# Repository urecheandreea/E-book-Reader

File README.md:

# E-book-Reader
## Hardware 
**OpenBook** is an open-source, portable e-reader powered by the **ESP32-C6-WROOM-1-N8** microcontroller.
### Microcontroller - **ESP32-C6-WROOM-1-N8**
  - 32-bit RISC-V @ 160 MHz
  - 8MB internal flash
  - Supports **Wi-Fi 6 (802.11ax)** and **Bluetooth 5.0 LE**
  - Interfaces used:
    - **SPI** (for E-Ink display, Flash, SD card)
    - **I2C** (for sensors and RTC)
    - **UART**, **GPIO**, **PWM**
### E-Ink Display
- **E-Ink screen** connected via SPI:
  - MOSI: GPIO18  
  - MISO: GPIO19  
  - CLK: GPIO20  
  - CS: GPIO21  
- Power is controlled via MOSFET (Q3 - S1B126DT1-GE3) to save energy.
- Display type selection is done via jumper (S11, P2).
##  Storage
- **MicroSD Card**
  - Connected via SPI (CS: GPIO9)
  - Used for storing files and data logging
- **NOR Flash – W25Q512JVEIQ**
  - 64MB external flash via SPI
##  Sensors
- **BME688** – Measures temperature, pressure, humidity, and air quality  
- **DS3231SN** – High-precision Real-Time Clock (RTC)  
- **MAX17048G+T10** – Battery fuel gauge (State of Charge)
- All sensors are connected via the **I2C** bus:
  - SDA: GPIO6  
  - SCL: GPIO7  
##  Power Management
- **USB-C connector**
  - Used for charging and possible data transfer
  - Includes CC identification and ESD protection
- **MCP73831** – LiPo battery charging IC
- **XC6220A331MR-G** – Low dropout regulators for 3.3V power
- EPD and I2C power rails are individually controlled via MOSFETs
- ESD protection on USB and SPI lines (USBLC6-2SC6Y, SD05B05V2L)
## Interfaces & Expandability
- **QWIIC / Stemma QT connector**
  - Easy expansion via plug-and-play I2C modules
- **Test Pads**
  - Breakout access to GPIO, UART, I2C for debugging
- **Control buttons**
  - RESET and BOOT
- **Status LEDs** for user feedback

## Power Consumption Summary
| Component              | Active (mA) | Sleep (mA) | Notes                             |
|-----------------------|-------------|------------|-----------------------------------|
| **ESP32-C6**          | ~80–100     | ~0.02      | Depends on Wi-Fi & sleep mode     |
| **E-Paper Display**   | ~26         | ~0.01      | Only during refresh               |
| **BME688 Sensor**     | ~2.1        | ~0.15      | Sleep mode available              |
| **RTC DS3231**        | ~0.2        | ~0.2       | Constant low power                |
| **MicroSD Card**      | ~30–100     | ~0.2       | Depends on access frequency       |
| **W25Q512JVEIQ Flash**| ~10–20      | ~0.01      | During SPI read/write             |
## ESP32-C6 Pin Usage
| Component              | ESP32-C6 Pin(s)                          | Interface | Purpose                                                             |
|------------------------|------------------------------------------|-----------|---------------------------------------------------------------------|
| E-Paper Display        | GPIO7 (MOSI), GPIO6 (SCK), GPIO10 (CS), GPIO5 (DC), GPIO23 (RST), GPIO3 (BUSY) | SPI | Transfers image data to the display and controls its state         |
| MicroSD Card           | GPIO7 (MOSI), GPIO6 (SCK), GPIO4 (CS_SD), GPIO2 (MISO)                        | SPI | Allows storage and retrieval of e-book files                        |
| BME688 Sensor          | GPIO21 (SDA), GPIO22 (SCL)                                                   | I2C | Reads temperature, humidity, pressure, and air quality             |
| RTC Module (DS3231)    | GPIO21 (SDA), GPIO22 (SCL), GPIO18 (RST), GPIO1 (32KHz, optional), GPIO0 (INT_RTC, optional) | I2C | Keeps track of time even when the ESP32 is off                     |
| NOR Flash (W25Q512J)   | GPIO11 (CS_FLASH), GPIO6 (SCK), GPIO2 (MISO), GPIO7 (MOSI)                   | SPI | Additional non-volatile storage                                     |
| Battery Fuel Gauge     | GPIO21 (SDA), GPIO22 (SCL)                                                   | I2C | Monitors battery level and charge status                            |
| USB-C Connector        | Via LDO regulator to 3.3V power rail                                          | USB | Supplies power and programming interface for the ESP32-C6          |
| Control Buttons        | GPIO9 (BOOT), GPIO15 (CHANGE), EN (RESET)                                    | GPIO | User input for device interaction and hardware reset                |

## Block Diagram

## Bill Of Materials
| Component                            | Link                                                                                             | Datasheet                                                                 |
|-------------------------------------|--------------------------------------------------------------------------------------------------|---------------------------------------------------------------------------|
| ESP32-C6-WROOM-1-N8                 | [SnapEDA](https://www.snapeda.com/parts/ESP32-C6-WROOM-1-N8/Espressif+Systems/view-part/?ref=eda) | [Datasheet](https://www.snapeda.com/parts/ESP32-C6-WROOM-1-N8/Espressif%20Systems/datasheet/) |
| MCP73831T-2ACI/OT – PMIC            | [SnapEDA](https://www.snapeda.com/parts/MCP73831T-2ACI/OT/Microchip/datasheet/)                  | [Datasheet](https://www.snapeda.com/parts/MCP73831T-2ACI/OT/Microchip/datasheet/)             |
| MAX17048G+T10 – Fuel Gauge          | [SnapEDA](https://www.snapeda.com/parts/MAX17048G+T10/Analog+Devices/view-part/?ref=eda)         | [Datasheet](https://www.snapeda.com/parts/MAX17048G+T10/Analog%20Devices/datasheet/)          |
| BME680 – Environmental Sensor       | [SnapEDA](https://www.snapeda.com/parts/BME680/Bosch/view-part/?welcome=home)                    | [Datasheet](https://www.bosch-sensortec.com/media/boschsensortec/downloads/datasheets/bst-bme680-ds001.pdf) |
| DS3231SN – RTC                      | [SnapEDA](https://www.snapeda.com/parts/DS3231SN%23/Analog+Devices/view-part/?ref=eda)           | [Datasheet](https://www.snapeda.com/parts/DS3231SN%23/Analog%20Devices/datasheet/)            |
| W25Q512JVEIQ – SPI Flash            | [SnapEDA](https://www.snapeda.com/parts/W25Q512JVEIQ/Winbond+Electronics/view-part/?ref=eda)    | [Datasheet](https://www.winbond.com/resource-files/W25Q512JV%20SPI%20RevB%2006252019%20KMS.pdf) |
| QWIIC Connector                     | [SnapEDA](https://www.snapeda.com/parts/PRT-14417/SparkFun/view-part/)                          | [Datasheet](https://www.snapeda.com/parts/PRT-14417/SparkFun%20Electronics/datasheet/)        |
| USB4110-GF-A – USB-C Connector      | [ComponentSearchEngine](https://componentsearchengine.com/part-view/USB4110-GF-A/GCT%20(GLOBAL%20CONNECTOR%20TECHNOLOGY)) | [Datasheet](https://gct.co/files/drawings/usb4110.pdf) |
| FH34SRJ-24S-0.5SH – FFC Connector   | [Mouser](https://ro.mouser.com/ProductDetail/Hirose-Connector/FH34SRJ-24S-0.5SH99?qs=vcbW%252B4%252BSTIpKBl5ap9J8Fw%3D%3D) | [Datasheet](https://www.snapeda.com/parts/FH34SRJ-24S-0.5SH(99)/Hirose%20Connector/datasheet/) |
| KP-1608SURCK – LED 0603             | [SnapEDA](https://www.snapeda.com/parts/KP-1608SURCK/Kingbright/view-part/?ref=search&t=LED%200603) | [Datasheet](https://www.snapeda.com/parts/KP-1608SURCK/Kingbright/datasheet/)                |
| EVQPUJ02K – Custom Button           | [Panasonic](https://industry.panasonic.com/global/en/products/control/switch/light-touch/number/evqpuj02k) | [Datasheet](https://industry.panasonic.com/global/en/downloads?tab=catalog&small_g_cd=203&part_no=EVQPUJ02K) |
| CPH3225A – RTC Crystal              | [SnapEDA](https://www.snapeda.com/parts/CPH3225A/Seiko+Instruments/view-part/?ref=snap)          | [Datasheet](https://www.snapeda.com/parts/CPH3225A/Seiko%20Instruments/datasheet/)            |
| BD5229G-TR – Reset IC               | [ComponentSearchEngine](https://componentsearchengine.com/part-view/BD5229G-TR/ROHM%20Semiconductor) | [Datasheet](https://fscdn.rohm.com/en/products/databook/datasheet/ic/power/voltage_detector/bd52xxg-e.pdf) |
| XC6220A331MR-G – LDO Regulator      | [ComponentSearchEngine](https://componentsearchengine.com/part-view/XC6220A331MR-G/Torex)         | [Datasheet](https://product.torexsemi.com/system/files/series/xc6220.pdf)                     |
| 744043680 – Inductor                | [Mouser](https://ro.mouser.com/ProductDetail/Wurth-Elektronik/744043680?qs=PGXP4M47uW6VkZq%252BkzjrHA%3D%3D) | [Datasheet](https://www.we-online.com/components/products/datasheet/744043680.pdf)            |
| SI1308EDL – MOSFET                  | [SnapEDA](https://www.snapeda.com/parts/SI1308EDL-T1-GE3/Vishay+Siliconix/view-part/?welcome=home&ref=eda) | [Datasheet](https://www.snapeda.com/parts/SI1308EDL-T1-GE3/Vishay%20Siliconix/datasheet/)     |
| MBR0530 – Schottky Diode           | [SnapEDA](https://www.snapeda.com/parts/MBR0530/Onsemi/view-part/?ref=snap)                      | [Datasheet](https://www.snapeda.com/parts/MBR0530/ON%20Semiconductor/datasheet/)              |
| USBLC6-2SC6Y – ESD Protection       | [SnapEDA](https://www.snapeda.com/parts/USBLC6-2SC6Y/STMicroelectronics/view-part/?welcome=home&ref=eda) | [Datasheet](https://www.snapeda.com/parts/USBLC6-2SC6Y/STMicroelectronics/datasheet/)         |
| PGB1010603MR – TVS Protection       | [SnapEDA](https://www.snapeda.com/parts/PGB1010603MR/Littelfuse/view-part/?ref=eda)              | [Datasheet](https://www.snapeda.com/parts/PGB1010603MR/Littelfuse%20Inc./datasheet/)          |
| 112A-TAAR-R03 – Pin Header          | [Comet](https://store.comet.srl.ro/Catalogue/Product/43497/)                                     | [Datasheet](https://www.snapeda.com/parts/112A-TAAR-R03/Attend/datasheet/)                    |
| 0402 Ceramic Capacitor             | [Mouser](https://ro.mouser.com/c/passive-components/capacitors/ceramic-capacitors/?q=CC0402)     | [Datasheet](https://componentsearchengine.com/Datasheets/2/CC0402MRX5R5BB106.pdf)             |
| 0402 Resistor                      | [GrabCAD](https://grabcad.com/library/resistor-0402-1)                                            | [Datasheet](https://www.yageo.com/upload/media/product/products/datasheet/rchip/PYu-RC_Group_51_RoHS_L_12.pdf) |
| TAJB475K025RNJ – 3528 Tantalum Cap | [SnapEDA](https://www.snapeda.com/parts/TAJB475K025RNJ/AVX%20Corporation/view-part/?ref=eda)     | [Datasheet](https://s3.amazonaws.com/snapeda/datasheet/TAJB475K025RNJ_AVX.pdf)               |
| SJ -SMD solder JUMPER              | [GrabCAD](https://grabcad.com/library/solder-jumpers-1)                                          | [DataSheet](https://www.farnell.com/datasheets/2813407.pdf)                                  |
| PFMF.050.1-ESP32C6_VARISTORCN1812  | [Mouser](https://www.mouser.co.uk/ProductDetail/EPCOS-TDK/B72520T0350K062?qs=dEfas%2FXlABIszF52uu7vrg%3D%3D)| [DataSheet](https://www.tdk-electronics.tdk.com/inf/75/db/CTVS_14/Surge_protection_series.pdf)  | 

## Implementation Steps
Creating the schematic according to the diagram,Finding and loading 3D models for each component,Designing the PCB,Placing the components on the PCB,Routing,Creating ground planes, via-stitching,Meeting requirements (component names on top silkscreen, DRC clean, etc.),Creating the battery and display,Assembling everything into the enclosure.

I only approved the "SMD-Hole, Board Outline Clearance" errors, as this was previously accepted and specified.

## Issues encountered:
I had to manually add the 3D model for EACH component because I had problems and errors when trying to update the library (adding to the library wasn't working), which was extremely time-consuming.

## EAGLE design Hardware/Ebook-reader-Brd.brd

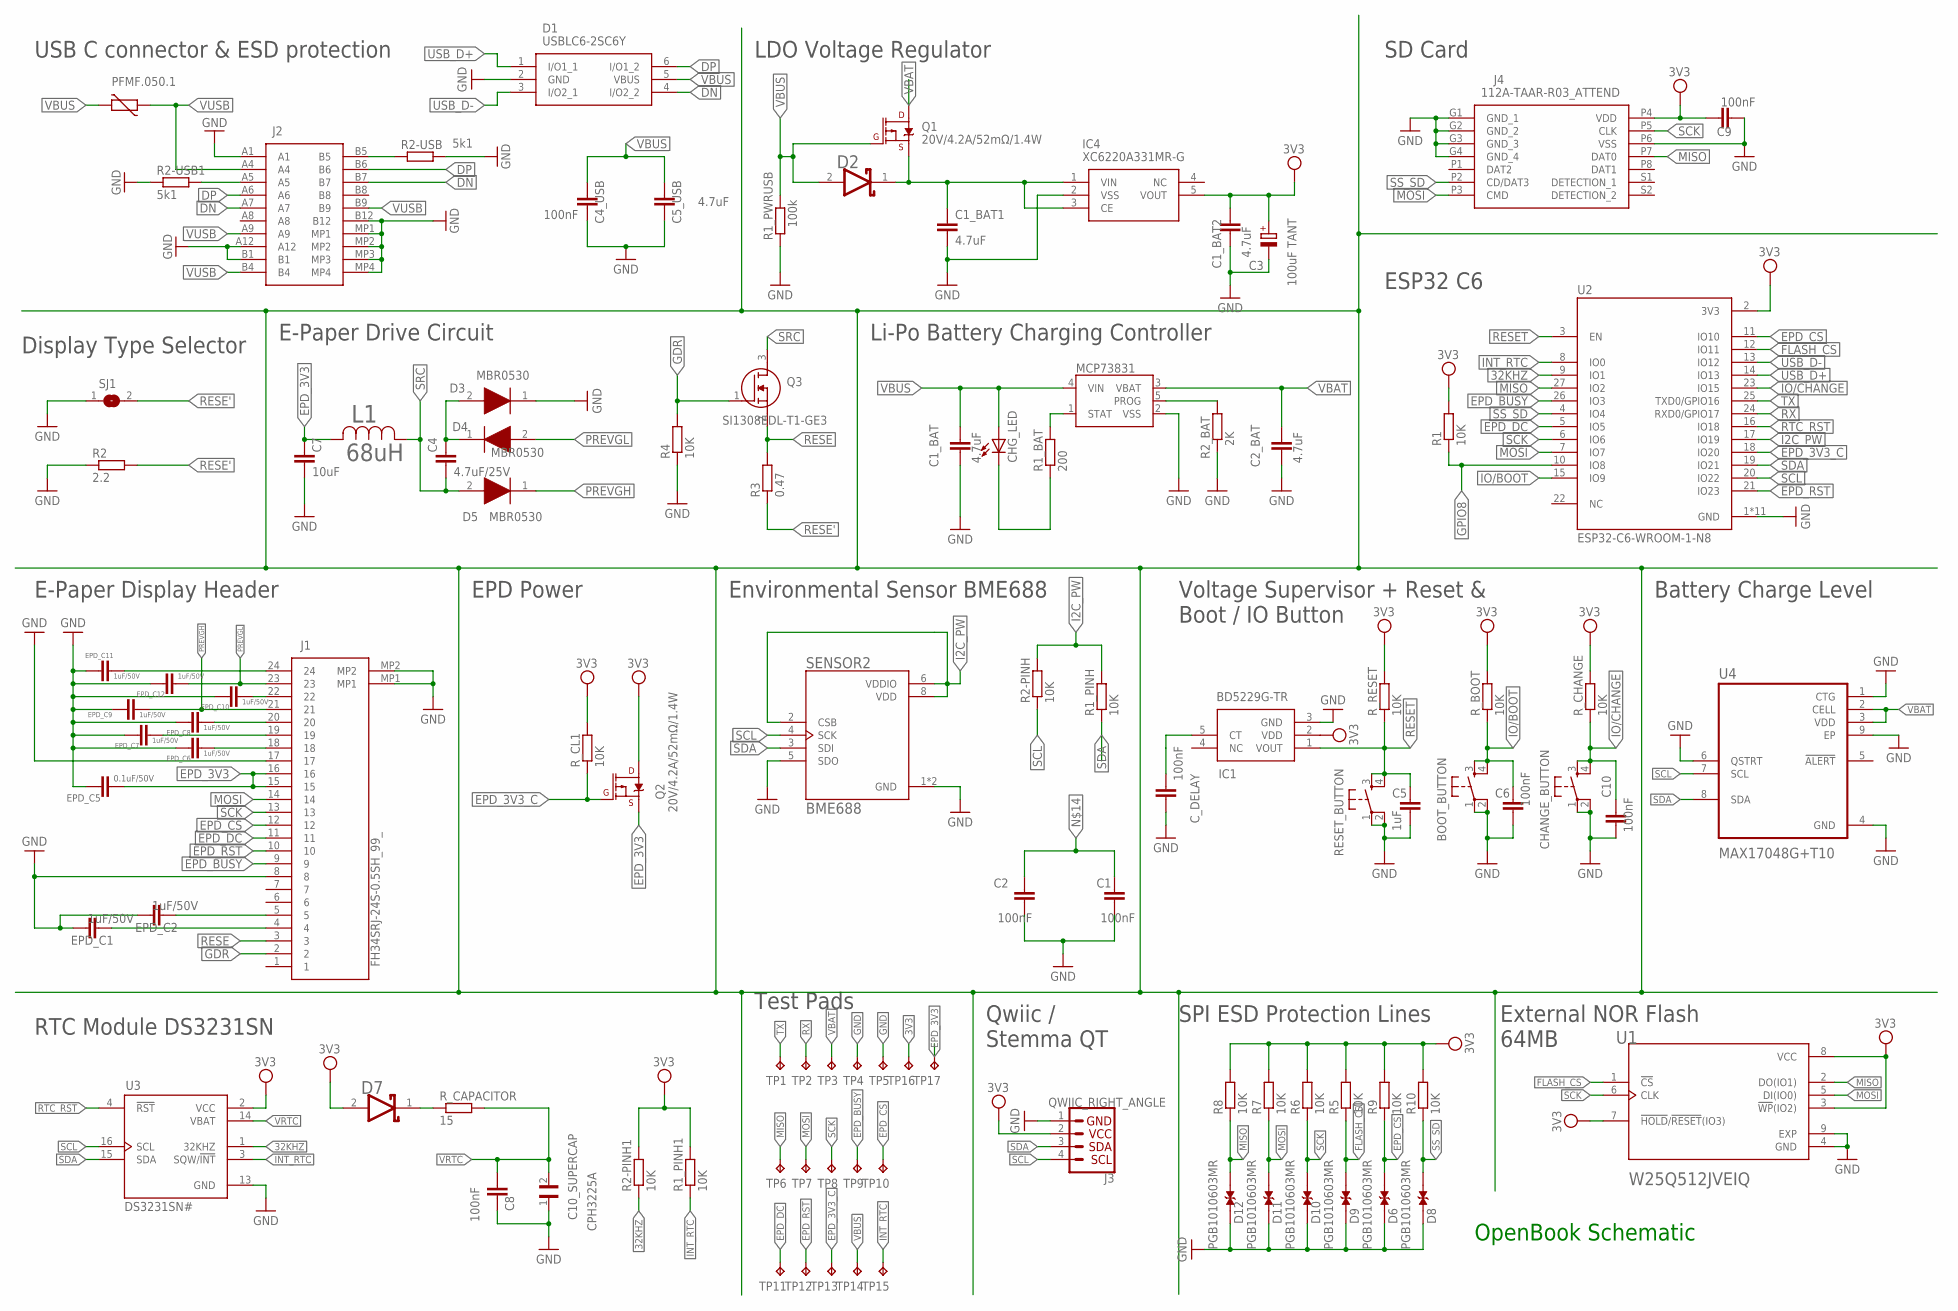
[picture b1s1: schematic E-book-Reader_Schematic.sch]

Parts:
BOOT_BUTTON: BOOT_BUTTON; MYBUTTON
C1, C2, C6, C9, C10: 100nF; EAGLE-LTSPICE_C0402
C1_BAT, C1_BAT1, C1_BAT2, C2_BAT, C5_USB: 4.7uF; EAGLE-LTSPICE_C0402
C3: 100uF TANT; RCL_CT3528
C4: 4.7uF/25V; ESP32_WROVER_EAGLE-LTSPICE_C0402
C4_USB, C8: 100nF; ESP32_WROVER_EAGLE-LTSPICE_C0402
C5: 1uF; EAGLE-LTSPICE_C0402
C7: 10uF; ESP32_WROVER_EAGLE-LTSPICE_C0402
C10_SUPERCAP: CPH3225A; CAPCP3225X100N
CHANGE_BUTTON: CHANGE_BUTTON; MYBUTTON
CHG_LED: ADAFRUIT_LEDCHIP-LED0603; ADAFRUIT_CHIP-LED0603
C_DELAY: 100nF; EAGLE-LTSPICE_C0402
D1: USBLC6-2SC6Y; SOT95P280X145-6N
D2: ESP32_WROVER_AVX---SD0805S020S1R0_AVX_SD0805S020S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; ESP32_WROVER_AVX---SD0805S020S1R0_AVX_SD0805S020S1R0_0
D3, D4, D5: MBR0530; SOD3716X135N
D6, D8, D9, D10, D11, D12: PGB1010603MR; DIOC1608X36N
D7: SD0805S020S1R0; ESP32_WROVER_AVX---SD0805S020S1R0_AVX_SD0805S020S1R0_0
EPD_C1, EPD_C2, EPD_C6, EPD_C7, EPD_C8, EPD_C9, EPD_C10, EPD_C11, EPD_C12: 1uF/50V; ESP32_WROVER_EAGLE-LTSPICE_C0402
EPD_C5: 0.1uF/50V; ESP32_WROVER_EAGLE-LTSPICE_C0402
IC1: BD5229G-TR; SOT95P280X125-5N
IC4: XC6220A331MR-G; SOT95P280X120-5N
J1: FH34SRJ-24S-0.5SH_99_; FH34SRJ24S05SH99
J2: SAMACSYS_PARTS_USB4110-GF-A; SAMACSYS_PARTS_USB4110GFA
J3: QWIIC_RIGHT_ANGLE; JST04_1MM_RA
J4: 112A-TAAR-R03_ATTEND; 112ATAARR03ATTEND
L1: 68uH; IND_4828-WE-TPC_WRE
MCP73831: ESP32_WROVER_SPARKFUN-IC-POWER_MCP73831; ESP32_WROVER_SPARKFUN-IC-POWER_SOT23-5
PFMF.050.1: ESP32C6_VARISTORCN1812; ESP32C6_VARISTOR_CT/CN1812
Q1, Q2: 20V/4.2A/52mΩ/1.4W; ESP32_WROVER_SPARKFUN-DISCRETESEMI_SOT23-3
Q3: SI1308EDL-T1-GE3; SOT65P210X110-3N
R1, R1_PINH, R1_PINH1, R2-PINH, R2-PINH1, R4, R5, R6, R7, R8, R9, R10: 10K; ESP32_WROVER_EAGLE-LTSPICE_R0402
R1_BAT: 200; ESP32_WROVER_EAGLE-LTSPICE_R0402
R1_PWRUSB: 100k; ESP32_WROVER_EAGLE-LTSPICE_R0402
R2: 2.2; ESP32_WROVER_EAGLE-LTSPICE_R0402
R2-USB, R2-USB1: 5k1; ESP32_WROVER_EAGLE-LTSPICE_R0402
R2_BAT: 2K; ESP32_WROVER_EAGLE-LTSPICE_R0402
R3: 0.47; ESP32_WROVER_EAGLE-LTSPICE_R0402
RESET_BUTTON: RESET_BUTTON; MYBUTTON
R_BOOT: 10K; ESP32_WROVER_EAGLE-LTSPICE_R0402
R_CAPACITOR: 15; ESP32_WROVER_EAGLE-LTSPICE_R0402
R_CHANGE: 10K; ESP32_WROVER_EAGLE-LTSPICE_R0402
R_CL1: 10K; ESP32_WROVER_EAGLE-LTSPICE_R0402
R_RESET: 10K; ESP32_WROVER_EAGLE-LTSPICE_R0402
SENSOR2: BME688; ESP32_WROVER_BME680_PSON80P300X300X100-8N
SJ1: SJ
TP1, TP2, TP3, TP4, TP5, TP6, TP7, TP8, TP9, TP10, TP11, TP12, TP13, TP14, TP15, TP16, TP17: TPTP20R; TP20R
U1: W25Q512JVEIQ; SON127P600X800X80-9N
U2: ESP32-C6-WROOM-1-N8; XCVR_ESP32-C6-WROOM-1-N8
U3: DS3231SN#; SOIC127P1032X265-16N
U4: MAX17048G+T10; SON50P200X200X80-9N

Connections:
3V3: C1_BAT2.1, C3.+, C9.1, D7.2 (ANODE), IC1.2 (VDD), IC4.5 (VOUT), J3.2, J4.P4 (VDD), Q2.3 (D), R1.2, R1_PINH1.2, R2-PINH1.2, R5.2, R6.2, R7.2, R8.2, R9.2, R10.2, R_BOOT.2, R_CHANGE.2, R_CL1.2, R_RESET.2, TP16.TP, U1.3 (!WP!(IO2)), U1.7 (!HOLD!/!RESET!(IO3)), U1.8 (VCC), U2.2 (3V3), U3.2 (VCC)
32KHZ: R2-PINH1.1, U2.9 (IO1), U3.1 (32KHZ)
DN: D1.4 (I/O2_2), J2.A7, J2.B7
DP: D1.6 (I/O1_2), J2.A6, J2.B6
EPD_3V3: C7.1, EPD_C5.1, J1.15, J1.16, L1.2, Q2.2 (S), TP17.TP
EPD_3V3_C: Q2.1 (G), R_CL1.1, TP13.TP, U2.18 (IO20)
EPD_BUSY: J1.9, TP9.TP, U2.26 (IO3)
EPD_CS: D6.2, J1.12, R9.1, TP10.TP, U2.11 (IO10)
EPD_DC: J1.11, TP11.TP, U2.5 (IO5)
EPD_RST: J1.10, TP12.TP, U2.21 (IO23)
FLASH_CS: D9.2, R5.1, U1.1 (!CS), U2.12 (IO11)
GDR: J1.2, Q3.1 (G), R4.2
GND: BOOT_BUTTON.1, BOOT_BUTTON.2, C1.2, C1_BAT.2, C1_BAT1.2, C1_BAT2.2, C2.2, C2_BAT.2, C3.-, C4_USB.2, C5.2, C5_USB.2, C6.2, C7.2, C8.2, C9.2, C10.2, C10_SUPERCAP.1, CHANGE_BUTTON.1, CHANGE_BUTTON.2, C_DELAY.2, D1.2 (GND), D3.1 (K), D6.1, D8.1, D9.1, D10.1, D11.1, D12.1, EPD_C1.2, EPD_C2.2, EPD_C5.2, EPD_C6.2, EPD_C7.2, EPD_C8.2, EPD_C9.2, EPD_C10.2, EPD_C11.2, EPD_C12.2, IC1.3 (GND), IC4.2 (VSS), J1.8, J1.17, J1.MP1, J1.MP2, J2.A1, J2.A12, J2.B1, J2.B12, J2.MP1, J2.MP2, J2.MP3, J2.MP4, J3.1, J4.G1 (GND_1), J4.G2 (GND_2), J4.G3 (GND_3), J4.G4 (GND_4), J4.P6 (VSS), MCP73831.2 (VSS), R1_PWRUSB.1, R2.1, R2-USB.2, R2-USB1.1, R2_BAT.1, R4.1, RESET_BUTTON.1, RESET_BUTTON.2, SENSOR2.1 (GND), SENSOR2.5 (SDO), SENSOR2.7 (GND), SJ1.1, TP4.TP, TP5.TP, U1.4 (GND), U1.9 (EXP), U2.1 (GND), U2.28 (GND), U2.29_1 (GND), U2.29_2 (GND), U2.29_3 (GND), U2.29_4 (GND), U2.29_5 (GND), U2.29_6 (GND), U2.29_7 (GND), U2.29_8 (GND), U2.29_9 (GND), U3.13 (GND), U4.1 (CTG), U4.4 (GND), U4.6 (QSTRT), U4.9 (EP)
GPIO8: R1.1, U2.10 (IO8)
I2C_PW: R1_PINH.2, R2-PINH.2, SENSOR2.2 (CSB), SENSOR2.6 (VDDIO), SENSOR2.8 (VDD), U2.17 (IO19)
INT_RTC: R1_PINH1.1, TP15.TP, U2.8 (IO0), U3.3 (SQW/!INT)
IO/BOOT: BOOT_BUTTON.3, BOOT_BUTTON.4, C6.1, R_BOOT.1, U2.15 (IO9)
IO/CHANGE: C10.1, CHANGE_BUTTON.3, CHANGE_BUTTON.4, R_CHANGE.1, U2.23 (IO15)
MISO: D12.2, J4.P7 (DAT0), R8.1, TP6.TP, U1.2 (DO(IO1)), U2.27 (IO2)
MOSI: D11.2, J1.14, J4.P3 (CMD), R7.1, TP7.TP, U1.5 (DI(IO0)), U2.7 (IO7)
unnamed: MCP73831.5 (PROG), R2_BAT.2
unnamed: C4.1, D3.2 (A), D4.1 (K)
unnamed: J2.A5, R2-USB1.2
unnamed: C1_BAT1.1, D2.1 (CATHODE), IC4.1 (VIN), IC4.3 (CE), Q1.2 (S)
unnamed: MCP73831.1 (STAT), R1_BAT.2
unnamed: CHG_LED.C, R1_BAT.1
unnamed: EPD_C1.1, J1.4
unnamed: EPD_C2.1, J1.5
unnamed: J2.B5, R2-USB.1
unnamed: EPD_C10.1, J1.22
unnamed: C_DELAY.1, IC1.5 (CT)
unnamed: C1.1, C2.1
unnamed: D7.1 (CATHODE), R_CAPACITOR.1
unnamed: EPD_C8.1, J1.20
unnamed: EPD_C11.1, J1.24
unnamed: EPD_C7.1, J1.19
unnamed: EPD_C6.1, J1.18
PREVGH: D5.1 (K), EPD_C9.1, J1.21
PREVGL: D4.2 (A), EPD_C12.1, J1.23
RESE: J1.3, Q3.2 (S), R3.2
RESE': R2.2, R3.1, SJ1.2
RESET: C5.1, IC1.1 (VOUT), RESET_BUTTON.3, RESET_BUTTON.4, R_RESET.1, U2.3 (EN)
RTC_RST: U2.16 (IO18), U3.4 (!RST)
RX: TP2.TP, U2.24 (RXD0/GPIO17)
SCK: D10.2, J1.13, J4.P5 (CLK), R6.1, TP8.TP, U1.6 (CLK), U2.6 (IO6)
SCL: J3.4, R2-PINH.1, SENSOR2.4 (SCK), U2.20 (IO22), U3.16 (SCL), U4.7 (SCL)
SDA: J3.3, R1_PINH.1, SENSOR2.3 (SDI), U2.19 (IO21), U3.15 (SDA), U4.8 (SDA)
SRC: C4.2, D5.2 (A), L1.1, Q3.3 (D)
SS_SD: D8.2, J4.P2 (CD/DAT3), R10.1, U2.4 (IO4)
TX: TP1.TP, U2.25 (TXD0/GPIO16)
USB_D+: D1.1 (I/O1_1), U2.14 (IO13)
USB_D-: D1.3 (I/O2_1), U2.13 (IO12)
VBAT: C2_BAT.1, MCP73831.3 (VBAT), Q1.3 (D), TP3.TP, U4.2 (CELL), U4.3 (VDD)
VBUS: C1_BAT.1, C4_USB.1, C5_USB.1, CHG_LED.A, D1.5 (VBUS), D2.2 (ANODE), MCP73831.4 (VIN), PFMF.050.1.2, Q1.1 (G), R1_PWRUSB.2, TP14.TP
VRTC: C8.1, C10_SUPERCAP.2, R_CAPACITOR.2, U3.14 (VBAT)
VUSB: J2.A4, J2.A9, J2.B4, J2.B9, PFMF.050.1.1

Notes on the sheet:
USB C connector & ESD protection
LDO Voltage Regulator
SD Card
Display Type Selector
E-Paper Drive Circuit
Li-Po Battery Charging Controller
ESP32 C6
E-Paper Display Header
EPD Power
Environmental Sensor BME688
Voltage Supervisor + Reset & Boot / IO Button
Battery Charge Level
RTC Module DS3231SN
Test Pads
Qwiic / Stemma QT
SPI ESD Protection Lines
External NOR Flash 64MB
OpenBook Schematic

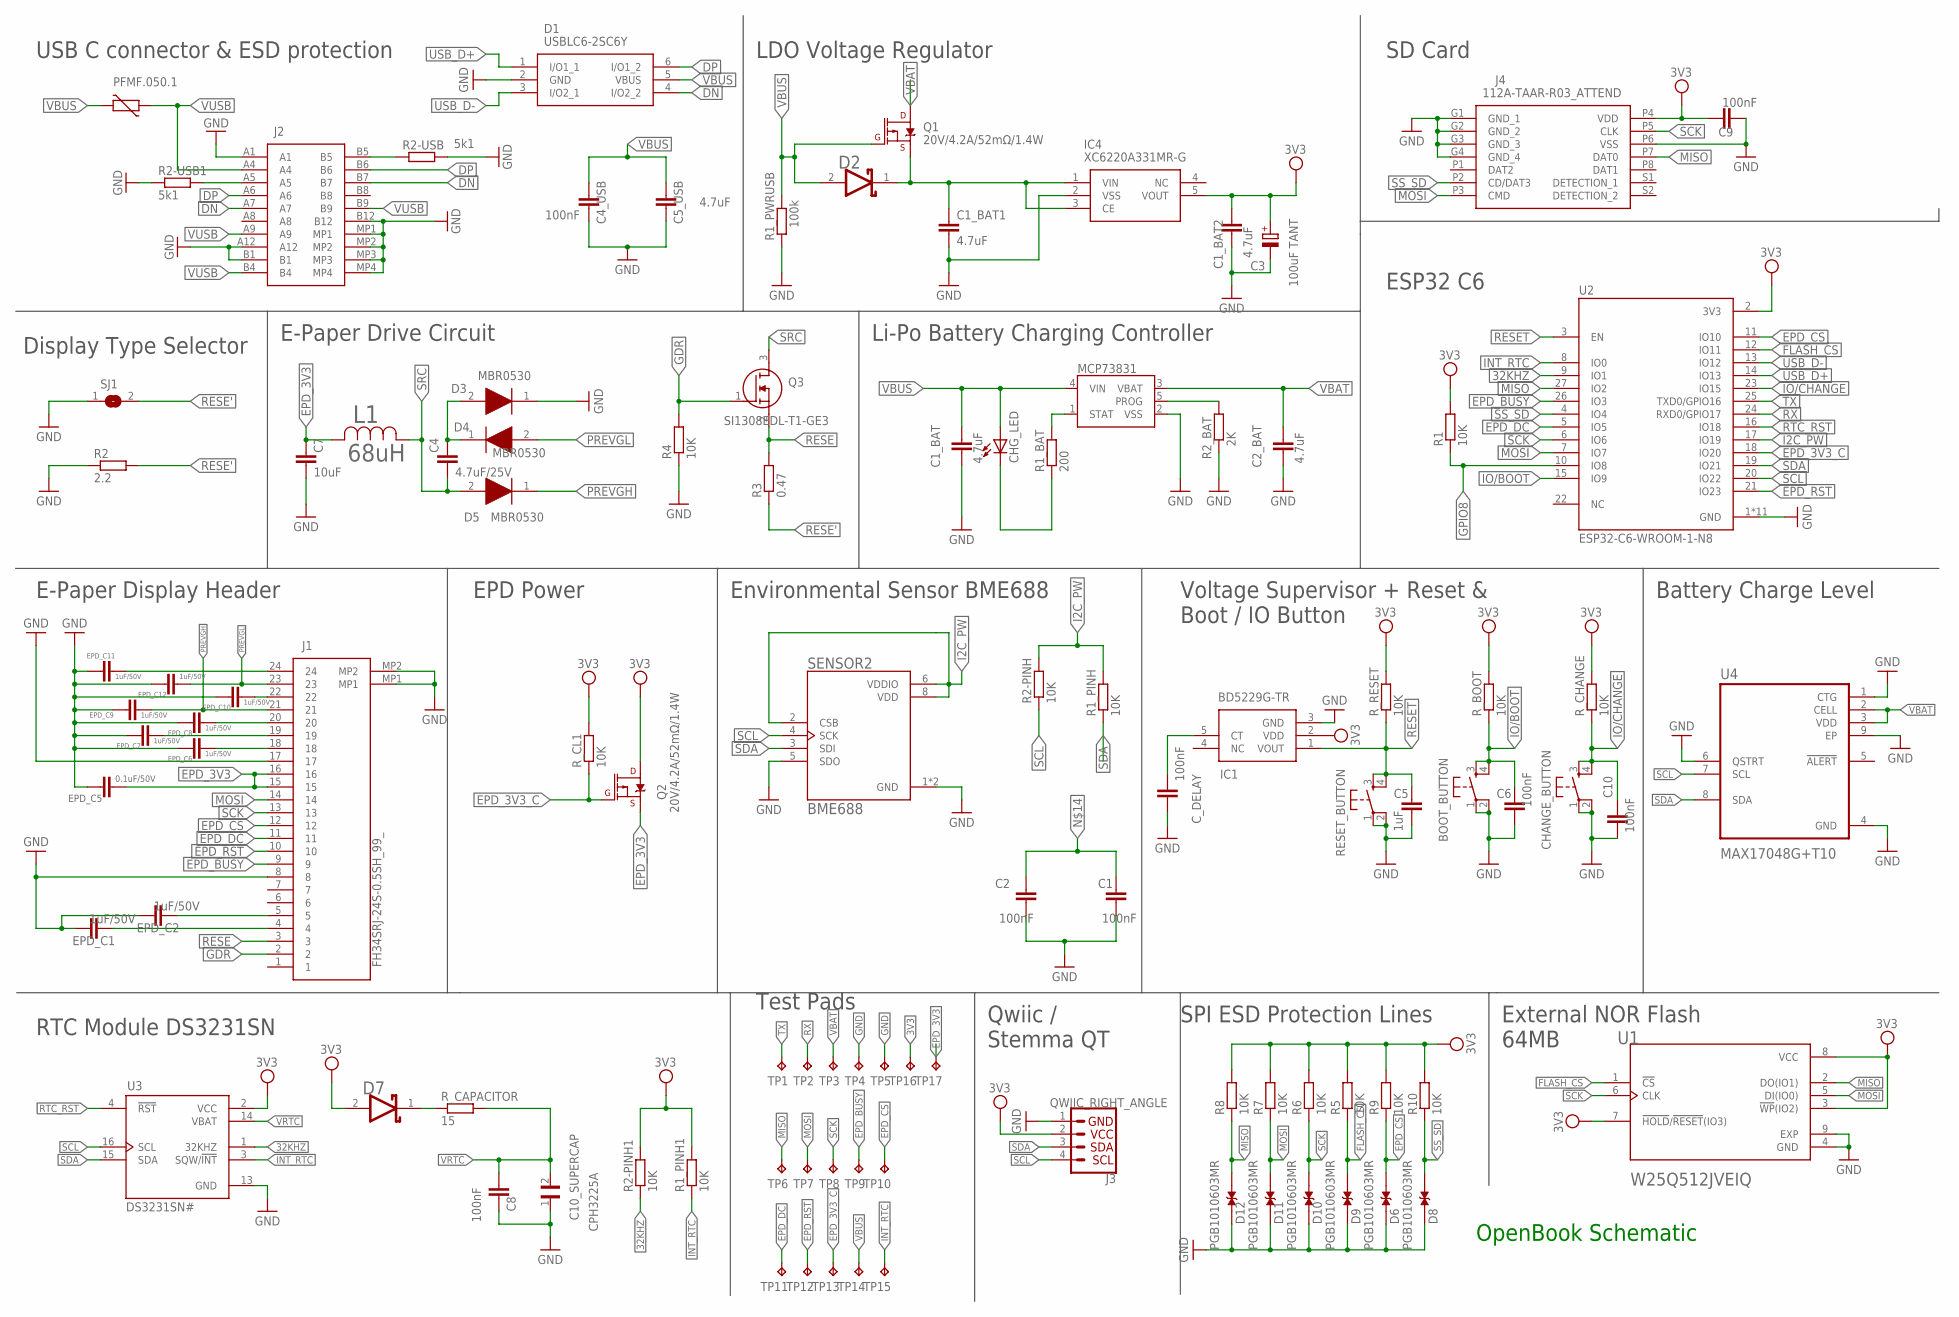
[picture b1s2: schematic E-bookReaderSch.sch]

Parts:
BOOT_BUTTON: BOOT_BUTTON; MYBUTTON
C1, C2, C6, C9, C10: 100nF; EAGLE-LTSPICE_C0402
C1_BAT, C1_BAT1, C1_BAT2, C2_BAT, C5_USB: 4.7uF; EAGLE-LTSPICE_C0402
C3: 100uF TANT; RCL_CT3528
C4: 4.7uF/25V; ESP32_WROVER_EAGLE-LTSPICE_C0402
C4_USB, C8: 100nF; ESP32_WROVER_EAGLE-LTSPICE_C0402
C5: 1uF; EAGLE-LTSPICE_C0402
C7: 10uF; ESP32_WROVER_EAGLE-LTSPICE_C0402
C10_SUPERCAP: CPH3225A; CAPCP3225X100N
CHANGE_BUTTON: CHANGE_BUTTON; MYBUTTON
CHG_LED: ADAFRUIT_LEDCHIP-LED0603; ADAFRUIT_CHIP-LED0603
C_DELAY: 100nF; EAGLE-LTSPICE_C0402
D1: USBLC6-2SC6Y; SOT95P280X145-6N
D2: ESP32_WROVER_AVX---SD0805S020S1R0_AVX_SD0805S020S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; ESP32_WROVER_AVX---SD0805S020S1R0_AVX_SD0805S020S1R0_0
D3, D4, D5: MBR0530; SOD3716X135N
D6, D8, D9, D10, D11, D12: PGB1010603MR; DIOC1608X36N
D7: SD0805S020S1R0; ESP32_WROVER_AVX---SD0805S020S1R0_AVX_SD0805S020S1R0_0
EPD_C1, EPD_C2, EPD_C6, EPD_C7, EPD_C8, EPD_C9, EPD_C10, EPD_C11, EPD_C12: 1uF/50V; ESP32_WROVER_EAGLE-LTSPICE_C0402
EPD_C5: 0.1uF/50V; ESP32_WROVER_EAGLE-LTSPICE_C0402
IC1: BD5229G-TR; SOT95P280X125-5N
IC4: XC6220A331MR-G; SOT95P280X120-5N
J1: FH34SRJ-24S-0.5SH_99_; FH34SRJ24S05SH99
J2: SAMACSYS_PARTS_USB4110-GF-A; SAMACSYS_PARTS_USB4110GFA
J3: QWIIC_RIGHT_ANGLE; JST04_1MM_RA
J4: 112A-TAAR-R03_ATTEND; 112ATAARR03ATTEND
L1: 68uH; IND_4828-WE-TPC_WRE
MCP73831: ESP32_WROVER_SPARKFUN-IC-POWER_MCP73831; ESP32_WROVER_SPARKFUN-IC-POWER_SOT23-5
PFMF.050.1: ESP32C6_VARISTORCN1812; ESP32C6_VARISTOR_CT/CN1812
Q1, Q2: 20V/4.2A/52mΩ/1.4W; ESP32_WROVER_SPARKFUN-DISCRETESEMI_SOT23-3
Q3: SI1308EDL-T1-GE3; SOT65P210X110-3N
R1, R1_PINH, R1_PINH1, R2-PINH, R2-PINH1, R4, R5, R6, R7, R8, R9, R10: 10K; ESP32_WROVER_EAGLE-LTSPICE_R0402
R1_BAT: 200; ESP32_WROVER_EAGLE-LTSPICE_R0402
R1_PWRUSB: 100k; ESP32_WROVER_EAGLE-LTSPICE_R0402
R2: 2.2; ESP32_WROVER_EAGLE-LTSPICE_R0402
R2-USB, R2-USB1: 5k1; ESP32_WROVER_EAGLE-LTSPICE_R0402
R2_BAT: 2K; ESP32_WROVER_EAGLE-LTSPICE_R0402
R3: 0.47; ESP32_WROVER_EAGLE-LTSPICE_R0402
RESET_BUTTON: RESET_BUTTON; MYBUTTON
R_BOOT: 10K; ESP32_WROVER_EAGLE-LTSPICE_R0402
R_CAPACITOR: 15; ESP32_WROVER_EAGLE-LTSPICE_R0402
R_CHANGE: 10K; ESP32_WROVER_EAGLE-LTSPICE_R0402
R_CL1: 10K; ESP32_WROVER_EAGLE-LTSPICE_R0402
R_RESET: 10K; ESP32_WROVER_EAGLE-LTSPICE_R0402
SENSOR2: BME688; ESP32_WROVER_BME680_PSON80P300X300X100-8N
SJ1: SJ
TP1, TP2, TP3, TP4, TP5, TP6, TP7, TP8, TP9, TP10, TP11, TP12, TP13, TP14, TP15, TP16, TP17: TPTP20R; TP20R
U1: W25Q512JVEIQ; SON127P600X800X80-9N
U2: ESP32-C6-WROOM-1-N8; XCVR_ESP32-C6-WROOM-1-N8
U3: DS3231SN#; SOIC127P1032X265-16N
U4: MAX17048G+T10; SON50P200X200X80-9N

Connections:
3V3: C1_BAT2.1, C3.+, C9.1, D7.2 (ANODE), IC1.2 (VDD), IC4.5 (VOUT), J3.2, J4.P4 (VDD), Q2.3 (D), R1.2, R1_PINH1.2, R2-PINH1.2, R5.2, R6.2, R7.2, R8.2, R9.2, R10.2, R_BOOT.2, R_CHANGE.2, R_CL1.2, R_RESET.2, TP16.TP, U1.3 (!WP!(IO2)), U1.7 (!HOLD!/!RESET!(IO3)), U1.8 (VCC), U2.2 (3V3), U3.2 (VCC)
32KHZ: R2-PINH1.1, U2.9 (IO1), U3.1 (32KHZ)
DN: D1.4 (I/O2_2), J2.A7, J2.B7
DP: D1.6 (I/O1_2), J2.A6, J2.B6
EPD_3V3: C7.1, EPD_C5.1, J1.15, J1.16, L1.2, Q2.2 (S), TP17.TP
EPD_3V3_C: Q2.1 (G), R_CL1.1, TP13.TP, U2.18 (IO20)
EPD_BUSY: J1.9, TP9.TP, U2.26 (IO3)
EPD_CS: D6.2, J1.12, R9.1, TP10.TP, U2.11 (IO10)
EPD_DC: J1.11, TP11.TP, U2.5 (IO5)
EPD_RST: J1.10, TP12.TP, U2.21 (IO23)
FLASH_CS: D9.2, R5.1, U1.1 (!CS), U2.12 (IO11)
GDR: J1.2, Q3.1 (G), R4.2
GND: BOOT_BUTTON.1, BOOT_BUTTON.2, C1.2, C1_BAT.2, C1_BAT1.2, C1_BAT2.2, C2.2, C2_BAT.2, C3.-, C4_USB.2, C5.2, C5_USB.2, C6.2, C7.2, C8.2, C9.2, C10.2, C10_SUPERCAP.1, CHANGE_BUTTON.1, CHANGE_BUTTON.2, C_DELAY.2, D1.2 (GND), D3.1 (K), D6.1, D8.1, D9.1, D10.1, D11.1, D12.1, EPD_C1.2, EPD_C2.2, EPD_C5.2, EPD_C6.2, EPD_C7.2, EPD_C8.2, EPD_C9.2, EPD_C10.2, EPD_C11.2, EPD_C12.2, IC1.3 (GND), IC4.2 (VSS), J1.8, J1.17, J1.MP1, J1.MP2, J2.A1, J2.A12, J2.B1, J2.B12, J2.MP1, J2.MP2, J2.MP3, J2.MP4, J3.1, J4.G1 (GND_1), J4.G2 (GND_2), J4.G3 (GND_3), J4.G4 (GND_4), J4.P6 (VSS), MCP73831.2 (VSS), R1_PWRUSB.1, R2.1, R2-USB.2, R2-USB1.1, R2_BAT.1, R4.1, RESET_BUTTON.1, RESET_BUTTON.2, SENSOR2.1 (GND), SENSOR2.5 (SDO), SENSOR2.7 (GND), SJ1.1, TP4.TP, TP5.TP, U1.4 (GND), U1.9 (EXP), U2.1 (GND), U2.28 (GND), U2.29_1 (GND), U2.29_2 (GND), U2.29_3 (GND), U2.29_4 (GND), U2.29_5 (GND), U2.29_6 (GND), U2.29_7 (GND), U2.29_8 (GND), U2.29_9 (GND), U3.13 (GND), U4.1 (CTG), U4.4 (GND), U4.6 (QSTRT), U4.9 (EP)
GPIO8: R1.1, U2.10 (IO8)
I2C_PW: R1_PINH.2, R2-PINH.2, SENSOR2.2 (CSB), SENSOR2.6 (VDDIO), SENSOR2.8 (VDD), U2.17 (IO19)
INT_RTC: R1_PINH1.1, TP15.TP, U2.8 (IO0), U3.3 (SQW/!INT)
IO/BOOT: BOOT_BUTTON.3, BOOT_BUTTON.4, C6.1, R_BOOT.1, U2.15 (IO9)
IO/CHANGE: C10.1, CHANGE_BUTTON.3, CHANGE_BUTTON.4, R_CHANGE.1, U2.23 (IO15)
MISO: D12.2, J4.P7 (DAT0), R8.1, TP6.TP, U1.2 (DO(IO1)), U2.27 (IO2)
MOSI: D11.2, J1.14, J4.P3 (CMD), R7.1, TP7.TP, U1.5 (DI(IO0)), U2.7 (IO7)
unnamed: MCP73831.5 (PROG), R2_BAT.2
unnamed: C4.1, D3.2 (A), D4.1 (K)
unnamed: J2.A5, R2-USB1.2
unnamed: C1_BAT1.1, D2.1 (CATHODE), IC4.1 (VIN), IC4.3 (CE), Q1.2 (S)
unnamed: MCP73831.1 (STAT), R1_BAT.2
unnamed: CHG_LED.C, R1_BAT.1
unnamed: EPD_C1.1, J1.4
unnamed: EPD_C2.1, J1.5
unnamed: J2.B5, R2-USB.1
unnamed: EPD_C10.1, J1.22
unnamed: C_DELAY.1, IC1.5 (CT)
unnamed: C1.1, C2.1
unnamed: D7.1 (CATHODE), R_CAPACITOR.1
unnamed: EPD_C8.1, J1.20
unnamed: EPD_C11.1, J1.24
unnamed: EPD_C7.1, J1.19
unnamed: EPD_C6.1, J1.18
PREVGH: D5.1 (K), EPD_C9.1, J1.21
PREVGL: D4.2 (A), EPD_C12.1, J1.23
RESE: J1.3, Q3.2 (S), R3.2
RESE': R2.2, R3.1, SJ1.2
RESET: C5.1, IC1.1 (VOUT), RESET_BUTTON.3, RESET_BUTTON.4, R_RESET.1, U2.3 (EN)
RTC_RST: U2.16 (IO18), U3.4 (!RST)
RX: TP2.TP, U2.24 (RXD0/GPIO17)
SCK: D10.2, J1.13, J4.P5 (CLK), R6.1, TP8.TP, U1.6 (CLK), U2.6 (IO6)
SCL: J3.4, R2-PINH.1, SENSOR2.4 (SCK), U2.20 (IO22), U3.16 (SCL), U4.7 (SCL)
SDA: J3.3, R1_PINH.1, SENSOR2.3 (SDI), U2.19 (IO21), U3.15 (SDA), U4.8 (SDA)
SRC: C4.2, D5.2 (A), L1.1, Q3.3 (D)
SS_SD: D8.2, J4.P2 (CD/DAT3), R10.1, U2.4 (IO4)
TX: TP1.TP, U2.25 (TXD0/GPIO16)
USB_D+: D1.1 (I/O1_1), U2.14 (IO13)
USB_D-: D1.3 (I/O2_1), U2.13 (IO12)
VBAT: C2_BAT.1, MCP73831.3 (VBAT), Q1.3 (D), TP3.TP, U4.2 (CELL), U4.3 (VDD)
VBUS: C1_BAT.1, C4_USB.1, C5_USB.1, CHG_LED.A, D1.5 (VBUS), D2.2 (ANODE), MCP73831.4 (VIN), PFMF.050.1.2, Q1.1 (G), R1_PWRUSB.2, TP14.TP
VRTC: C8.1, C10_SUPERCAP.2, R_CAPACITOR.2, U3.14 (VBAT)
VUSB: J2.A4, J2.A9, J2.B4, J2.B9, PFMF.050.1.1

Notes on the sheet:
USB C connector & ESD protection
LDO Voltage Regulator
SD Card
Display Type Selector
E-Paper Drive Circuit
Li-Po Battery Charging Controller
ESP32 C6
E-Paper Display Header
EPD Power
Environmental Sensor BME688
Voltage Supervisor + Reset & Boot / IO Button
Battery Charge Level
RTC Module DS3231SN
Test Pads
Qwiic / Stemma QT
SPI ESD Protection Lines
External NOR Flash 64MB
OpenBook Schematic

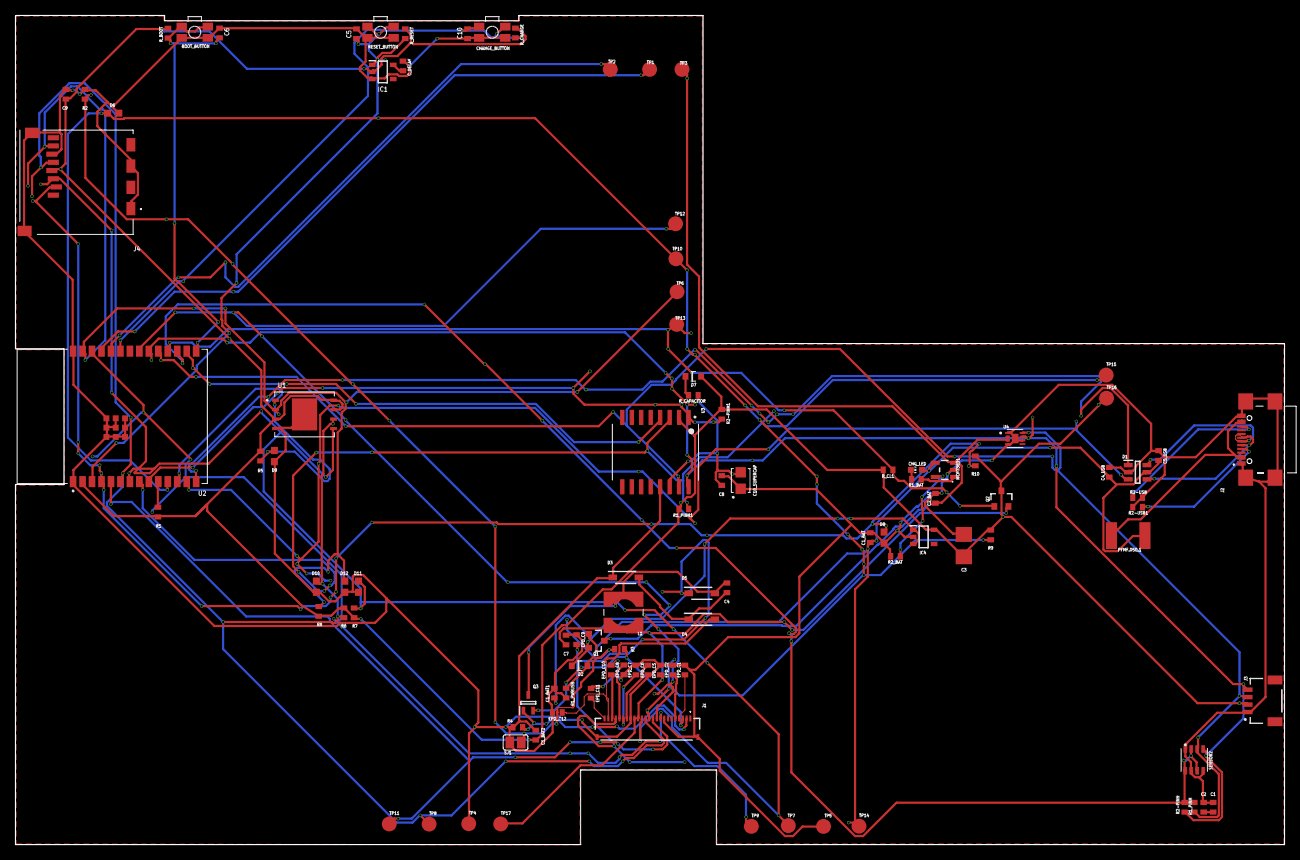
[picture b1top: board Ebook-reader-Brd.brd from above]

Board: 2 copper layers, 170.2 x 111.2 mm, 103 parts (0 on the bottom side), 56 nets.

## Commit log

2025-04-05 Create LICENSE

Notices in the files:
parts and their libraries:
DeskAssistant v19 v1: COPYRIGHT: Copyright (C) 2024 Ultra Librarian. All rights reserved.
